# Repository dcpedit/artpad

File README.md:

# ArtPad

Video: https://youtube.com/shorts/0jcIEa7Fye8

ArtPad is designed to be an artisian tray that also functions as a macro pad.  This repository contains two PCB designs.  `pcb` is the Choc hotswap version, and `pcb-chocmini` uses Choc Mini switches which can be built to be slightly thinner.  Both PCBs feature per-key RGB, an OLED display, and an optional rotary encoder.

## PCB Details
My original design uses Choc hotswap sockets which offers the most versatility since Choc switches come in a varity of flavors.  I later decided to design a slimmer version that uses Choc Mini switches, but limits you to only 3 types of switches (linear, tactile, and clicky) and is not hotswapable.  Below are the heights measured from the lowest point of the switch (pin) to the top of the keycap ([wrk pure](https://worklouder.cc/shop/wrk-pure/) from Work Louder).

| Choc PCB | Choc Mini PCB |
|----------|---------------|
| 13.5mm | 11mm |

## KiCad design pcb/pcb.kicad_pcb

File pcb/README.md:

# Choc Hotswap PCB
This PCB has not yet been tested

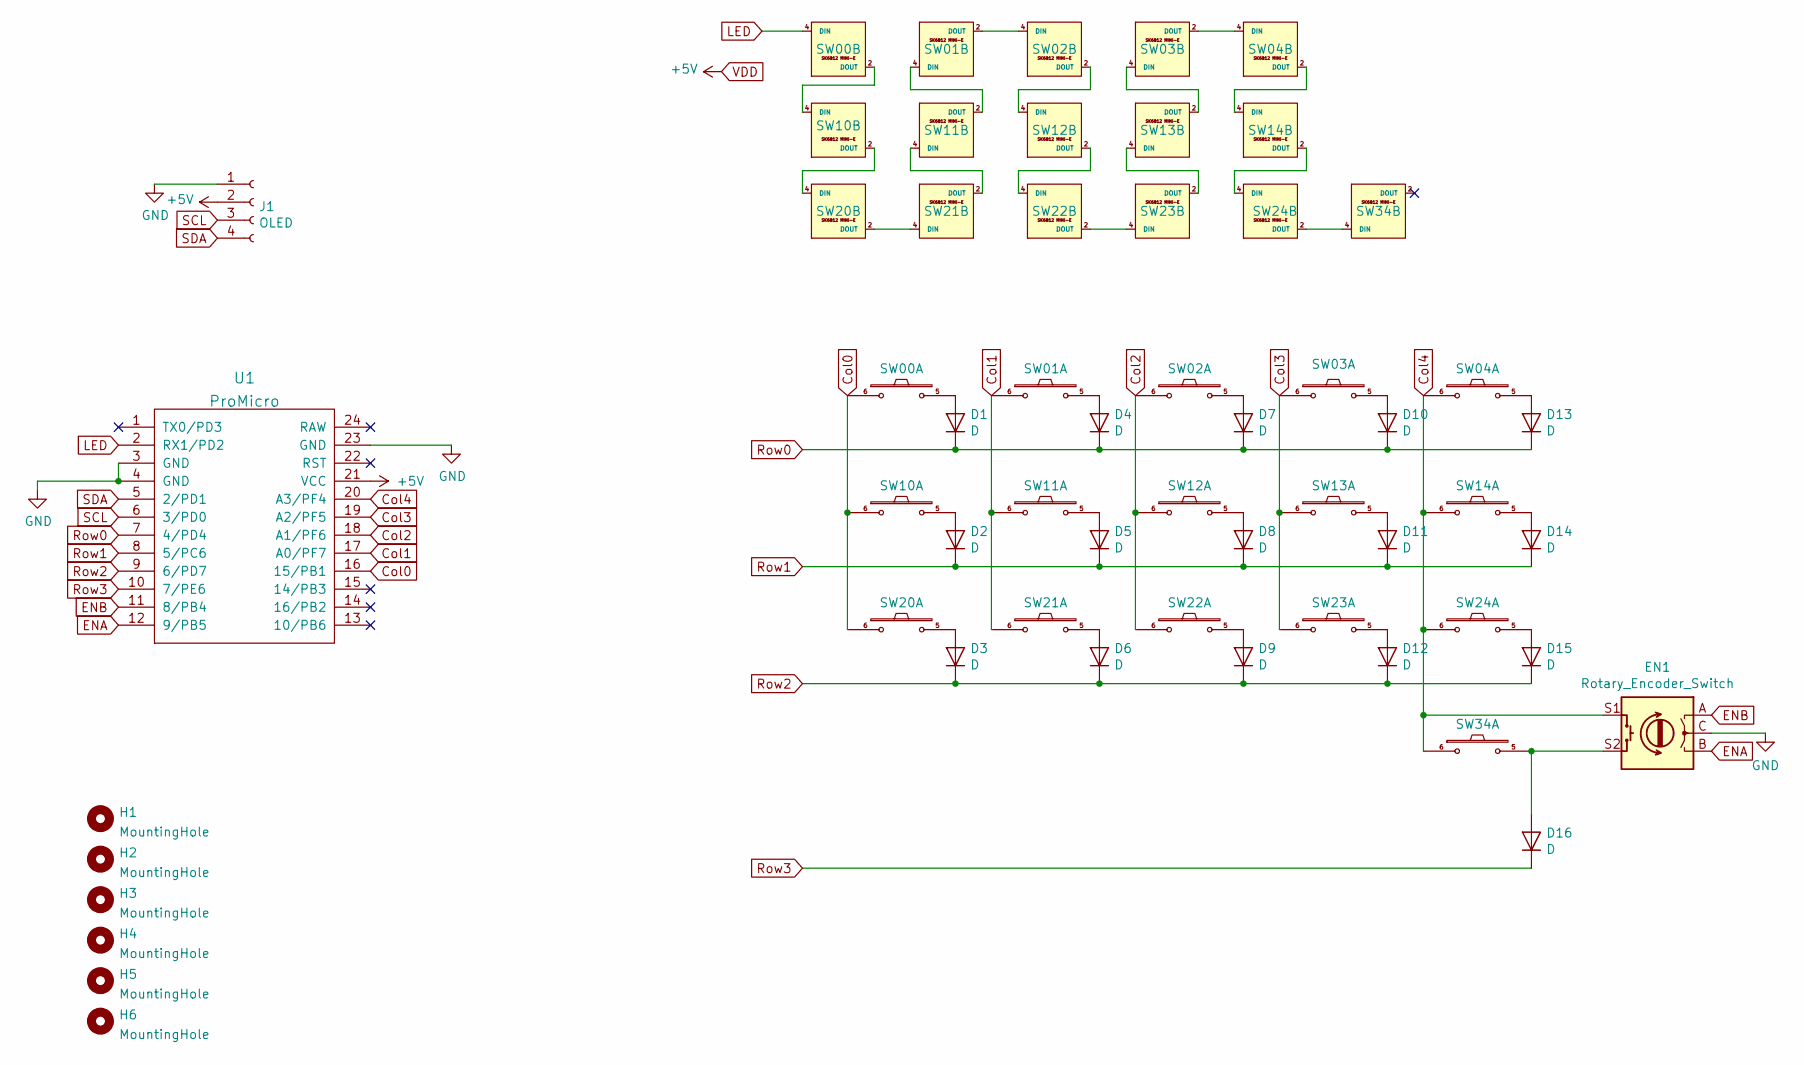
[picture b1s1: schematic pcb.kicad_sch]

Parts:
D1, D2, D3, D4, D5, D6, D7, D8, D9, D10, D11, D12, D13, D14, D15, D16: D; crkbd-diode
EN1: Rotary_Encoder_Switch; RotaryEncoder_Alps_EC11E-Switch_Vertical_H20mm
H1, H2, H3, H4, H5, H6: MountingHole
J1: OLED; SSD1306_OLED
SW00, SW01, SW02, SW03, SW04, SW10, SW11, SW12, SW13, SW14, SW20, SW21, SW22, SW23, SW24, SW34: SW_PUSH_LED; Choc_Hotswap_SK6812MiniE
U1: ProMicro

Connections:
Col0: SW00.6, SW10.6, SW20.6, U1.16 (15/PB1)
Col1: SW01.6, SW11.6, SW21.6, U1.17 (A0/PF7)
Col2: SW02.6, SW12.6, SW22.6, U1.18 (A1/PF6)
Col3: SW03.6, SW13.6, SW23.6, U1.19 (A2/PF5)
Col4: EN1.S1, SW04.6, SW14.6, SW24.6, SW34.6, U1.20 (A3/PF4)
ENA: EN1.B, U1.12 (9/PB5)
ENB: EN1.A, U1.11 (8/PB4)
GND: EN1.C, J1.1, SW00.3 (GND), SW01.3 (GND), SW02.3 (GND), SW03.3 (GND), SW04.3 (GND), SW10.3 (GND), SW11.3 (GND), SW12.3 (GND), SW13.3 (GND), SW14.3 (GND), SW20.3 (GND), SW21.3 (GND), SW22.3 (GND), SW23.3 (GND), SW24.3 (GND), SW34.3 (GND), U1.3 (GND), U1.4 (GND), U1.23 (GND)
LED: SW00.4 (DIN), U1.2 (RX1/PD2)
unnamed: D1.2 (A), SW00.5
unnamed: D2.2 (A), SW10.5
unnamed: D3.2 (A), SW20.5
unnamed: D4.2 (A), SW01.5
unnamed: D5.2 (A), SW11.5
unnamed: D6.2 (A), SW21.5
unnamed: D7.2 (A), SW02.5
unnamed: D8.2 (A), SW12.5
unnamed: D9.2 (A), SW22.5
unnamed: D10.2 (A), SW03.5
unnamed: D11.2 (A), SW13.5
unnamed: D12.2 (A), SW23.5
unnamed: D13.2 (A), SW04.5
unnamed: D14.2 (A), SW14.5
unnamed: D15.2 (A), SW24.5
unnamed: D16.2 (A), EN1.S2, SW34.5
unnamed: SW00.2 (DOUT), SW10.4 (DIN)
unnamed: SW01.2 (DOUT), SW02.4 (DIN)
unnamed: SW01.4 (DIN), SW11.2 (DOUT)
unnamed: SW02.2 (DOUT), SW12.4 (DIN)
unnamed: SW03.2 (DOUT), SW04.4 (DIN)
unnamed: SW03.4 (DIN), SW13.2 (DOUT)
unnamed: SW04.2 (DOUT), SW14.4 (DIN)
unnamed: SW10.2 (DOUT), SW20.4 (DIN)
unnamed: SW11.4 (DIN), SW21.2 (DOUT)
unnamed: SW12.2 (DOUT), SW22.4 (DIN)
unnamed: SW13.4 (DIN), SW23.2 (DOUT)
unnamed: SW14.2 (DOUT), SW24.4 (DIN)
unnamed: SW20.2 (DOUT), SW21.4 (DIN)
unnamed: SW22.2 (DOUT), SW23.4 (DIN)
unnamed: SW24.2 (DOUT), SW34.4 (DIN)
Row0: D1.1 (K), D4.1 (K), D7.1 (K), D10.1 (K), D13.1 (K), U1.7 (4/PD4)
Row1: D2.1 (K), D5.1 (K), D8.1 (K), D11.1 (K), D14.1 (K), U1.8 (5/PC6)
Row2: D3.1 (K), D6.1 (K), D9.1 (K), D12.1 (K), D15.1 (K), U1.9 (6/PD7)
Row3: D16.1 (K), U1.10 (7/PE6)
SCL: J1.3, U1.6 (3/PD0)
SDA: J1.4, U1.5 (2/PD1)
VDD: J1.2, SW00.1 (VDD), SW01.1 (VDD), SW02.1 (VDD), SW03.1 (VDD), SW04.1 (VDD), SW10.1 (VDD), SW11.1 (VDD), SW12.1 (VDD), SW13.1 (VDD), SW14.1 (VDD), SW20.1 (VDD), SW21.1 (VDD), SW22.1 (VDD), SW23.1 (VDD), SW24.1 (VDD), SW34.1 (VDD), U1.21 (VCC)

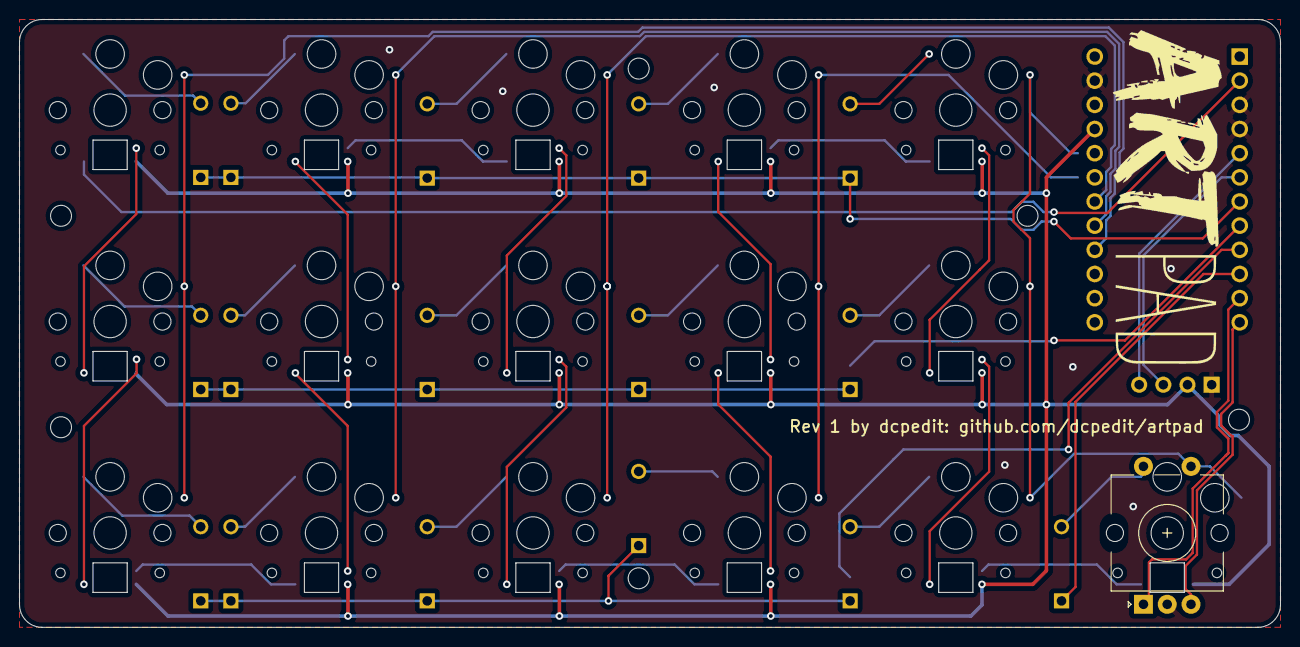
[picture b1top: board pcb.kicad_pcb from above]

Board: 2 copper layers, 132.6 x 63.9 mm, 41 parts (1 on the bottom side), 47 nets.

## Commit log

2023-04-10 Add readmes
2023-04-11 Clarify readme
